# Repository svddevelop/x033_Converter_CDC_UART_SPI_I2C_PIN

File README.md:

# USB programmable converter based on CH32X033

Using CDC (USB) connection you can

programmatically control interfaces

## Current commands
When the device is connected via USB, by connecting a terminal, you can get help on using the control commands. At the end of each command there must be a CR (0x0D) symbol.

### [help]
outputs information about possible commands.

### [print]
outputs the current configuration settings

### [helpuart]
commands for configuring the UART interface:

### [helpspi]
shows list of commands for configuring the SPI interface:

### [helpi2c]
shows list of commands for configuring the UART interface:

### [SAVE]

saves the current setting to the flash. On the next powrt connection of the device, this configuration will be automatic activated.

#### [SET:UART.DIS]
makes the UART interface unused.

##### [SET:UART.DIS]
activates the UART interface.

#### [SET:UART.BAUD=\<int value>]
Sets the communication speed for the UART interface. <int value> must be a value from 1200 to 2500000 baud per second.

Example: [SET:UART.BAUD=57600] - sets the communication speed to 57600.

### [SET:SPI.PRESC=\<char value>]
set the base clock prescaler:

BASE CLOCK = 48MHz /(2 << PRESC );

### [SET:SPI.BAUD=\<char value>]
makes division of base clock (see PRESC) with value:

  0	divede by 2,  
  1	divide by 4,  
  2	divide by 8,  
  3	divide by 16,  
  4	divide by 32,  
  5	divide by 54,  
  6	divide by 128,  
  7	divide by 256.  

#### [SET:SPI.DIS]
makes the SPI interface unused.

#### [SET:SPI.DIS]
activates the SPI interface.

#### [SET:SPI.CPOL=\<char val>]
set up the clock polarity (0 or 1); 

#### [SET:SPI.CPHA=\<char val>]
set up the clock phase (0 or 1); 

#### [TRN:\<dev src>-\<dev dst>.EN/DIS]
allow or disallow to transwer between interfaces where <dev src> and <dev dst> is:

  CDC, UART, SPI or I2C;
		
for example:

  [TRN:CDS-UART.EN] - allow a trafik from CDS to UART.
	
  [TRN:UART-UART.EN] - allow a trafik from UART to CDS.

---

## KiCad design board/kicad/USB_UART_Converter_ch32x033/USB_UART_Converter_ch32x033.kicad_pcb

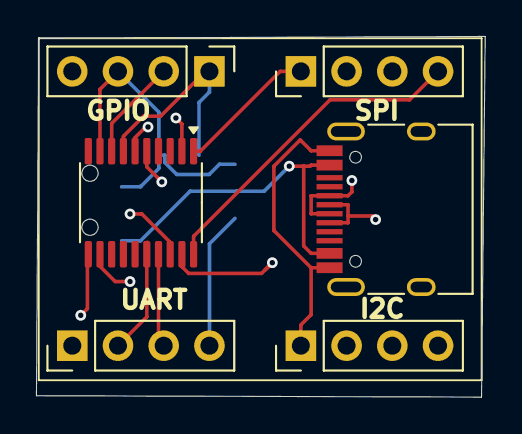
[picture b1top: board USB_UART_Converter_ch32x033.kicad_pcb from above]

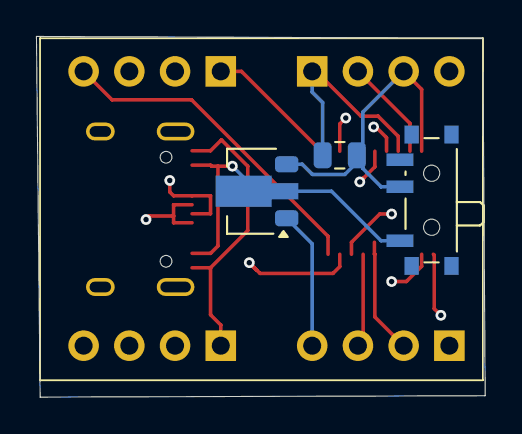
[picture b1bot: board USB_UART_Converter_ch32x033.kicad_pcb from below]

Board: 4 copper layers, 24.9 x 20.0 mm, 9 parts (3 on the bottom side), 15 nets.

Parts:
C1: 4,7µF; C_0805_2012Metric
J2: PRG; PinHeader_1x04_P2.54mm_Vertical
J3: U1; PinHeader_1x04_P2.54mm_Vertical
J4: I2C; PinHeader_1x04_P2.54mm_Vertical
J5: SPI; PinHeader_1x04_P2.54mm_Vertical
J7: USB_C_Receptacle_USB2.0_16P; USB_C_Receptacle_HRO_TYPE-C-31-M-12
SW2: SW_SPDT; SW_SPDT_PCM12
U1: TSSOP-20_4.4x6.5mm_P0.65mm
U3: HT75xx-1-SOT89; SOT-89-3

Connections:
+5: J4.4, J7.A4 (VBUS), J7.A9 (VBUS), J7.B4 (VBUS), J7.B9 (VBUS), SW2.1 (A), U3.2 (VIN)
DO: J2.2, U1.8 (PC18/DIO/TX3_/T2C1N_/T3C2_/I2C_/T1ET__)
GND: C1.2, J2.1, J3.4, J4.1, J7.A1 (GND), J7.A12 (GND), J7.B1 (GND), J7.B12 (GND), U1.7 (GND), U3.1 (GND)
I2C_SCL: J4.3, U1.12 (PA10/SCL/TX1_/MOSI_)
I2C_SDA: J4.2, U1.11 (PA11/SDA/SCK_/RX1_/C2P1)
RX1: J3.3, U1.17 (PA3/T2C4/T3C1_/RX2/O1O0/A3)
SPI_CS: J5.3, U1.19 (PA4/CS/O2O0/T3C2_/A4)
SPI_MISO: J5.1, U1.1 (PA6/MISO/T3C1/T1BK_/O1N0/A6_)
SPI_MOSI: J5.2, U1.2 (PA7/MOSI/T3C2/T1C1N_/O2P0/PB0/TX4/T1C2N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)
SPI_SCK: J5.4, U1.20 (PA5/SCK/TX4_1/O2N0/A5)
SWSCK: J2.4, U1.18 (PC19/DCK/T2C1_/T3C1_/I2C_/RX3_/C1P0)
TX1: J3.2, U1.16 (PA2/TX2/T2C3/O2O1/T2ET_/A2)
UDM: J7.A7 (D-), J7.B7 (D-), U1.5 (PC16/UDM/T1C4/TX4_2/I2C_/RX4_5/PC11)
UDP: J7.A6 (D+), J7.B6 (D+), U1.6 (PC17/UDP/TX4_5/I2C_/RX4_2/T1ET/PC10)
Vdd: C1.1, J2.3, J3.1, SW2.2 (B), U1.9 (VDD), U3.3 (VOUT)

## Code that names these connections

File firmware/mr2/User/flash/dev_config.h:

#pragma once

#ifdef __cplusplus
extern "C" {
#endif

/* pins 
 //uart
 PA2
 PA3

 //spi
 PA4
 PA5
 PA6
 PA7

 //i2c
 PA10
 PA11

 //gpio
 PC18
 PC19 //wo
 */ 

#define PIN_UART_RX         1
#define PIN_UART_TX         0

#define PIN_SPI_CS          2
#define PIN_SPI_SCK         3
#define PIN_SPI_MISO        4
#define PIN_SPI_MOSI        5

#define PIN_I2C_SCL         6
#define PIN_I2C_SDA         7

#define PIN_PIN_1           8
#define PIN_PIN_2           9


#define IS_PIN_UART(x)     ((x == 0)||(x == 1))
#define IS_PIN_SPI(x)      ((x == 2)||(x == 3)||(x == 4)||(x == 5))
#define IS_PIN_I2C(x)      ((x == 6)||(x == 7))
#define IS_PIN_PC19(x)      (x == 9)

 #define PINMODE_INP        0
 #define PINMODE_INPPD      1
 #define PINMODE_INPPU      2
 #define PINMODE_INPAN      3
 #define PINMODE_OUT        4     

#define SET_PIN_MODE(pin, mode) \
    ((mode) == 0 ? PIN_input(pin) : \
    ((mode) == 1 ? PIN_input_PD(pin) : \
    ((mode) == 2 ? PIN_input_PU(pin) : \
    ((mode) == 3 ? PIN_input_AN(pin) : \
     (mode) == 4 ? PIN_output(pin) : (void)0))))

#define GET_PIN_BY_INDEX(x) \
    ((x) == PIN_UART_TX ? PA2 : \
     (x) == PIN_UART_RX ? PA3 : \
     (x) == PIN_SPI_CS ? PA4 : \
     (x) == PIN_SPI_SCK ? PA5 : \
     (x) == PIN_SPI_MISO ? PA6 : \
     (x) == PIN_SPI_MOSI ? PA7 : \
     (x) == PIN_I2C_SCL ? PA10 : \
     (x) == PIN_I2C_SDA ? PA11 : \
     (x) == PIN_PIN_1 ? PC18 : \
     (x) == PIN_PIN_2 ? PC19 : 0)     

#include <stdint.h>
#include <stdbool.h>

typedef struct __attribute__((__packed__)){

    char uart:1;
    char spi:1;
    char i2c:1;

} cfg_active_intefaces_t;

typedef struct __attribute__((__packed__)){
    
    uint32_t baud;

} cfg_uart_t;

typedef struct __attribute__((__packed__)){

    uint8_t prescaller:4;
    uint8_t baud:3;
    char master: 1;
    char hw_cs: 1;
    char pha: 1;
    char pol: 1;

} cfg_spi_t;

typedef struct __attribute__((__packed__)){

    uint8_t cdc_uart:1;
    uint8_t uart_cdc:1;

    uint8_t cdc_spi:1;
    uint8_t spi_cdc:1;

    uint8_t cdc_i2c:1;
    uint8_t i2c_cdc:1;

    uint8_t spi_uart:1;
    uint8_t uart_spi:1;

    uint8_t i2c_uart:1;
    uint8_t uart_i2c:1;

    uint8_t spi_i2c:1;
    uint8_t i2c_spi:1;


} transfer_t;

typedef struct __attribute__((__packed__)){
    char mode: 4;
    //char interrupt: 4;

} cfg_pin_t;

typedef struct __attribute__((__packed__)){

        cfg_pin_t pa2;
        cfg_pin_t pa3;

        //spi
        cfg_pin_t pa4;
        cfg_pin_t pa5;
        cfg_pin_t pa6;
        cfg_pin_t pa7;

        //i2c
        cfg_pin_t pa10;
        cfg_pin_t pa11;

        //gpio
        cfg_pin_t pc18;
        cfg_pin_t pc19; //wo

} cfg_pins_t;


typedef struct __attribute__((__packed__,aligned(4))){

    uint8_t crc;
    cfg_active_intefaces_t active_interfaces;
    cfg_uart_t cfg_uart;
    cfg_spi_t cfg_spi;

    transfer_t trans;
    cfg_pins_t cfg_pins;

} configuration_t;


#define CFG_CRC_SIZE    (sizeof(configuration_t)-1)

#define CONF_FILL_CRC(x)    x.crc = 
void        onfiguration_init(configuration_t * a_inst);
bool        is_conf_valid(configuration_t * a_inst);
configuration_t conf_read_from_flash();
bool        conf_write_to_flash(configuration_t* a_conf);

void        cfg_uart_init(cfg_uart_t* a_conf);
void        cfg_spi_init(cfg_spi_t* a_conf);
void        cfg_pins_init(cfg_pins_t *a_conf);
void        cfg_init(configuration_t * a_conf);
void        activate_cfg(configuration_t * a_conf);
uint8_t     calc_cfg_crc(configuration_t * a_conf);

extern configuration_t global_conf;

#ifdef __cplusplus
}
#endif

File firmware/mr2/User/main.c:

// ===================================================================================
// Project:   Example for CH32X035/X034/X033
// Version:   v1.0
// Year:      2023
// Author:    Sergej Pfaffenrot, based on Stefan Wagner's code
// Github:    https://
// EasyEDA:   https://
// License:   http://creativecommons.org/licenses/by-sa/3.0/
// ===================================================================================
//
// Description:
// ------------
// Blink example.
//
// References:
// -----------
// - WCH Nanjing Qinheng Microelectronics: http://wch.cn
//
// Compilation Instructions:
// -------------------------
// - Make sure GCC toolchain (gcc-riscv64-unknown-elf, newlib) and Python3 with
//   chprog and rvprog (via pip) are installed. In addition, Linux requires access
//   rights to the USB bootloader.
// - Press the BOOT button on the MCU board and keep it pressed while connecting it
//   via USB to your PC.
// - Run 'make flash'.


// ===================================================================================
// Libraries, Definitions and Macros
// ===================================================================================

/*              PIN CONNECTION x033F8P6
 *
 * {7}          GND
 * {9}          Vdd
 *
 * {5} PC16/11  UDM
 * {6} PC17/10  UDP
 *
 * {8} PC18     SWDIO
 * {18}PC19     SWSCK
 *
 * {16}PA2      TX2
 * {17}PA3      RX2
 *
 * {2}PB0       TX4
 * {3}PB1       RX4
 *
 *
 *
 */



#include "system.h"                               // system functions
#include "gpio/gpio.h"                                 // GPIO functions
#include "USB/usb_cdc.h"
#include "uart/uart.h"

#include "flash/flash_userdata.h"
#include "sys/print.h"
#include <stdlib.h>
#include "flash/dev_config.h"
#include "cmd/cdc_cmd.h"


#define PIN_LED PB1                               // define LED pin

static char cdc_buffer[256];
static uint16_t cdc_buffer_len = 0;

#ifndef __code
#define __code const __attribute__((section(".rodata")))
#endif

configuration_t global_conf;


// ===================================================================================
// Main Function
// ===================================================================================
int main(void) {

    CLK_init();
    HSI_enable();
 



  // Setup
  //PIN_output(PIN_LED);                            // set LED pin to output
  
  CDC_init();

  //**************************************************************

    cfg_init(&global_conf);
    configuration_t loc ;

    read_struct_from_flash((char*)&loc, sizeof(configuration_t));
    
    uint8_t crc = calc_cfg_crc(&loc);

    if ( crc != loc.crc)
        cfg_init(&loc);
    else 
        global_conf = loc;

    activate_cfg(&global_conf);

  //**************************************************************

  // Loop
  while(1) {
    //PIN_toggle(PIN_LED);                          // toggle LED
    //DLY_ms(1);                                      // wait a bit

    int count = CDC_available();
    if (count ){

        if ( count > sizeof(cdc_buffer))
            count = sizeof(cdc_buffer);


        for (int i = 0; i < count; i++){
            cdc_buffer[i] = CDC_read();

        }
        cdc_buffer_len = count;

        if ( ifcmdexec(cdc_buffer, &global_conf ) ){

            count = 0;
            for(int i = 0; i < sizeof(cdc_buffer); i++ )
                cdc_buffer[i] = 0;

        }


        if ( count > 0 ){

            /*for (int i = 0; i < count; i++){


                char ch = cdc_buffer[i];
                UART2_write( ch );
                //CDC_write( ch ); // for test of buffer

                //UART4_write( ch );
            }*/

            process_cdc( &global_conf, cdc_buffer, &cdc_buffer_len );

        }
        CDC_flush();

    }

    process_uart( &global_conf );


    /*
    if ( UART2_available() ){

        CDC_write( UART2_read() );
        CDC_flush();
    }
    */
    /*
    if ( UART4_available() ){

        CDC_write( UART4_read() );
        CDC_flush();
    }
    */

  }
}

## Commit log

2025-09-30 README, img
2025-09-30 SPI integration; cdc_cmd - help, spi params;
2025-09-30 try user flash
2025-10-01 Load cfg on the start and activated it
2025-10-01 fix for set uart.baud
2025-10-01 readme.md + jpg
2025-10-01 reordered some files in the builds tree
2025-10-01 Versionsnummer; command TRN
2025-10-02 UART with IRQ works fine
2025-10-02 readme
2025-10-03 PINS funktional
2025-10-03 all need repair
2025-10-04 part with spi interface
2025-10-05 new command SET:CFG=<hexvalues>; the text in the cds_cmd has splited to diferents files with a extension '*.inc"
